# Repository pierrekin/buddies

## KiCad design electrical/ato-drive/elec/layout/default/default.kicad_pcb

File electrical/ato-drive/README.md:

# ato-drive — resonant PZT drive (atopile)

Parallel atopile exploration of the **product-generation resonant 1-bit drive**:
low-voltage battery rail, series-resonant tank, full-bridge keying.

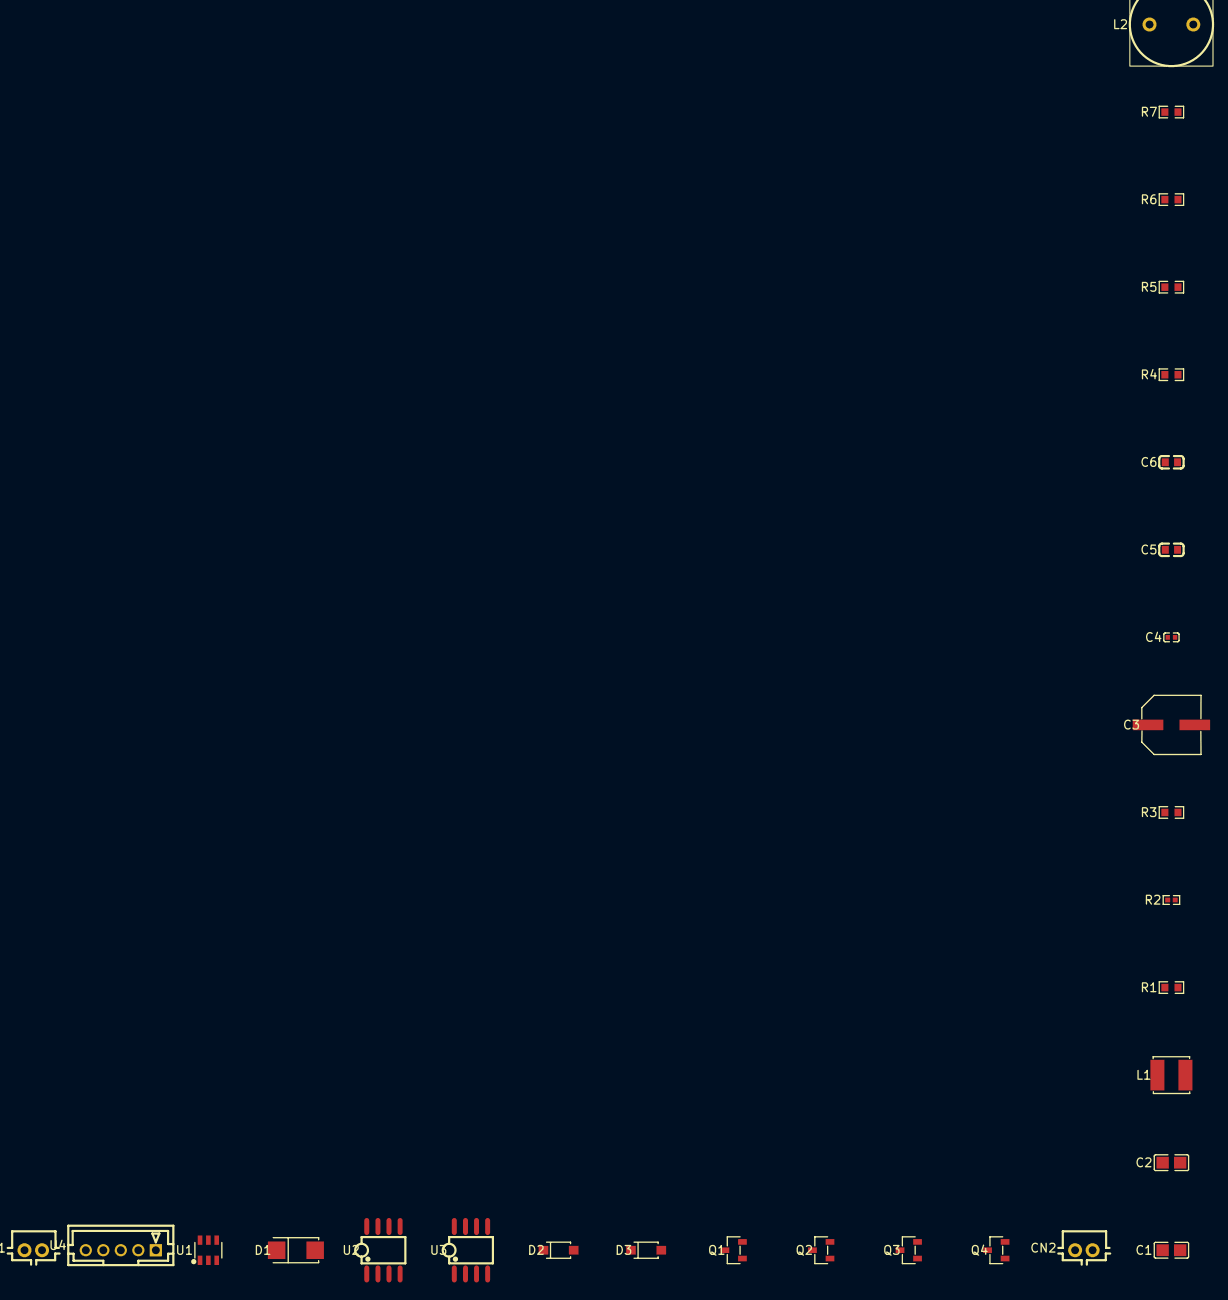
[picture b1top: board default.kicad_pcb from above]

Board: 2 copper layers, 28 parts (0 on the bottom side), 22 nets, no tracks yet.

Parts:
C1: 10µF ±10%; C0805
C2: 22µF ±20%; C0805
C3: 100µF ±20%; CAP-SMD_BD6.3-L6.6-W6.6-FD
C4: 1µF ±10%; C0402
C5, C6: 100nF ±10%; C0603
CN1, CN2: CONN-TH_B2B-PH-K-S
D1: SMA_L4.3-W2.6-LS5.2-RD
D2, D3: SOD-123F_L2.7-W1.6-LS3.8-RD
L1: L 10µH ±20%; IND-SMD_L4.0-W4.0
L2: L 560µH ±10%; IND-TH_BD9.5-P5.00-D0.7
Q1, Q2, Q3, Q4: SOT-23-3_L2.9-W1.3-P1.90-LS2.4-BR
R1: 10kΩ ±1%; R0603
R2: 100kΩ ±1%; R0402
R3: 200kΩ ±1%; R0603
R4, R5, R6, R7: 10Ω ±1%; R0603
U1: SOT-23-6_L2.9-W1.6-P0.95-LS2.8-BL
U2, U3: SOIC-8_L5.0-W4.0-P1.27-LS6.0-BL
U4: CONN-TH_B5B-PH-K-S-LF-SN

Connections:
1: CN2.1, L2.2
A: D1.2, L1.2, U1.1
FB: R1.1, R2.2, R3.2, U1.3
HO: R4.1, U2.7
LO: R5.1, U2.5
cboot_a-power-hv: C5.1, D2.1, U2.8
cboot_a-power-lv: C5.2, L2.1, Q1.2, Q2.3, U2.6
cboot_b-power-hv: C6.1, D3.1, U3.8
cboot_b-power-lv: C6.2, CN2.2, Q3.2, Q4.3, U3.6
ch.driver-HO: R6.1, U3.7
ch.driver-LO: R7.1, U3.5
cout-power-hv: C2.1, C3.1, C4.1, D1.1, Q1.3, Q3.3, R3.1
enable: U1.4, U2.3, U3.3, U4.3
g_ah: Q1.1, R4.2
g_al: Q2.1, R5.2
g_bh: Q3.1, R6.2
g_bl: Q4.1, R7.2
hv: C1.1, CN1.1, D2.2, D3.2, L1.1, U1.5, U2.1, U3.1
lv: C1.2, C2.2, C3.2, C4.2, CN1.2, Q2.2, Q4.2, R1.2, U1.2, U2.4, U3.4, U4.5
pwm_a: U2.2, U4.1
pwm_b: U3.2, U4.2
vset: R2.1, U4.4

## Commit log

2026-06-12 feat: initial commit
2026-06-12 feat: add rigid and damping masks
2026-06-12 feat: add beamforming simulation
2026-06-12 feat: add instrumentation
2026-06-12 feat: add direction finding
2026-06-12 chore: add gitkeep to captures/
2026-06-12 feat: add tracking simulation
2026-06-13 feat: add sonar sweep simulation
2026-06-13 feat: bump sonar sweep fidelity
2026-06-13 feat: add colors to sonar sweep
2026-06-13 feat: add multiple objects to sonar sweep
2026-06-13 feat: add diffuse bottom
2026-06-13 feat: add scaling args
2026-06-13 feat: add progress bar
2026-06-13 feat: add gpu support
2026-06-13 feat: add source precomputation
2026-06-13 feat: handle ctrl-c in viewer
2026-06-13 feat: pause viewer while scrubbing
2026-06-13 feat: snap play position on slider jump
2026-06-13 feat: add directional listing sonar
2026-06-13 feat: migrate captures to data/
2026-06-13 feat: add fine grained sliding
2026-06-13 feat: add buddies tool
2026-06-13 feat: remove viewer tool
2026-06-13 feat: add list items to buddies cli
2026-06-13 feat: add profiler
2026-06-13 feat: add folded masks and fuse velocity update
2026-06-13 fix: viewer teardown segfault
2026-06-13 feat: start viewer paused and add framestep
2026-06-13 feat: pin the viewer domain
2026-06-13 feat: add duration control to simulation
2026-06-13 fix: sea floor vs sea wall
2026-06-13 feat: parametise simulation boundary config
2026-06-13 feat: add cpml simulation boundary
2026-06-13 chore: remove useless labels
2026-06-13 chore: add sonal_listen4
2026-06-14 feat: add ook_link support
2026-06-14 feat: add ook eye diagram
2026-06-14 feat: add simulation extras and extensible view
2026-06-14 feat: add multi shot simulation to framework
2026-06-14 feat: add source digest to cli show
2026-06-14 feat: improve viewer layout
2026-06-14 feat: add model_link simulation
2026-06-14 feat: add simulation inspection tools
2026-06-14 feat: add beamforming comms
2026-06-14 feat: add ambient noise injection
2026-06-14 feat: add beamforming snr simulation
2026-06-15 feat: add lora with noise and spreading factor
2026-06-15 feat: add lora sync simulation
2026-06-15 feat: add wreck environment validation
2026-06-15 feat: add comms over nlos simulation
2026-06-15 fix: keep ambient noise sources clear of the sponge
2026-06-15 feat: measure noise floor with dedicated calibration shot
2026-06-15 feat: add firmware module
2026-06-15 feat: add hil harness
2026-06-16 feat: add hil display
2026-06-16 feat: add accoustics to hil
2026-06-16 feat: add hardware module
2026-06-16 feat: add hil tdoa model
2026-06-16 feat: add buddies pcb
2026-06-16 chore: cleanup atopile blinky project
2026-06-16 chore: organise project layout
2026-06-16 feat: add run script to firmware project
2026-06-16 chore: make skeleton for buddies electrical bringup
2026-06-17 feat: implement buddies ui
2026-06-17 feat: add blender project
2026-06-18 feat: amoled display
2026-06-18 feat: model enclosure and skeleton blender
2026-06-18 feat: add analogue parts to library
2026-06-18 feat: add buddy link simulation
2026-06-18 feat: add analytical notes
2026-06-18 chore: untrack glb meshes
2026-06-18 chore: untrack enclosure and rename display to buddy
2026-06-18 chore: untrack cube
2026-06-18 chore: refactor buddies model
2026-06-19 feat: improve export
2026-06-19 feat: add blender sync script
2026-06-20 feat: add sync to blender project
2026-06-20 feat: add tx resonant keying notes
2026-06-20 feat: add atto-drive experiment
